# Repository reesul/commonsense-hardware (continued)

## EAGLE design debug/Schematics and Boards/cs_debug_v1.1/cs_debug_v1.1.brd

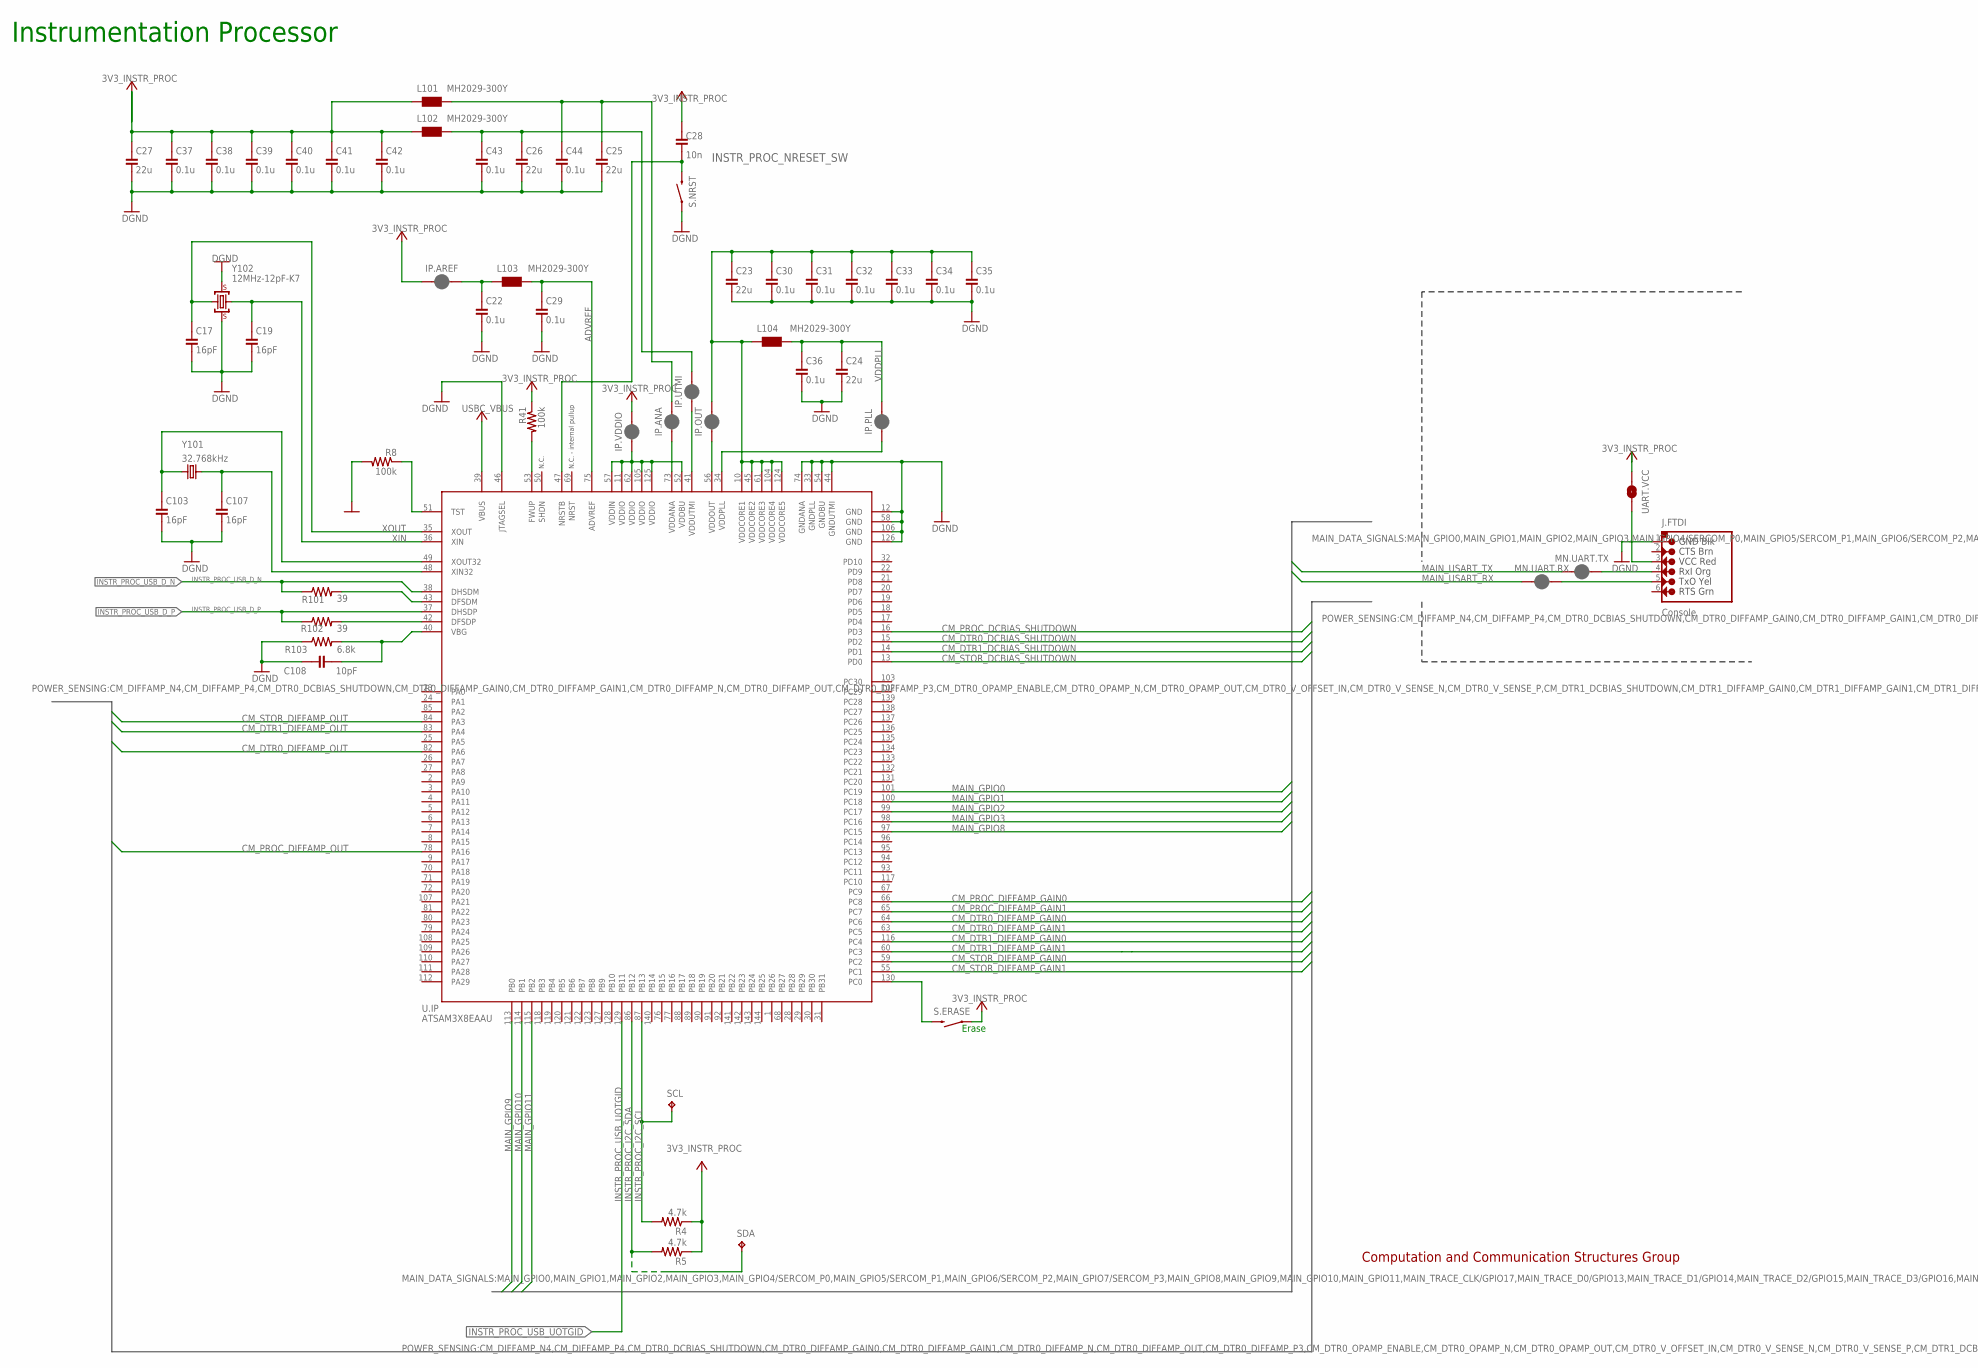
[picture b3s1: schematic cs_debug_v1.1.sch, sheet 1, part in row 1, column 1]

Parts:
C17, C19, C103, C107: 16pF; C0603; MPN C0603C160J5GACTU
C22, C29, C30, C31, C32, C33, C34, C35, C36, C37, C38, C39, C40, C41, C42, C43, C44: 0.1u; C0402; VOLTAGE 10V; MPN C0402C104K8RACTU
C23, C24, C25, C26, C27: 22u; C0805; VOLTAGE 10V; MPN C0805C226M8PAC7800
C28: 10n; C0402; MPN C0402C103K8RACTU
C108: 10pF; C0603; MPN C0603C100K8RAC7867
IP.ANA, IP.AREF, IP.OUT, IP.PLL, IP.UTMI, IP.VDDIO: JUMPER-SMT_2_NC_PASTE_NO-SILK; SMT-JUMPER_2_NC_PASTE_NO-SILK
J.FTDI: J-SERIAL-PORT; HEADER-1X6; PART_NO PH1-06-UA
L101, L102, L103, L104: MH2029-300Y; L0805; PART_NO MH2029-300Y
MN.UART.RX, MN.UART.TX: JUMPER-SMT_2_NC_PASTE_NO-SILK; SMT-JUMPER_2_NC_PASTE_NO-SILK
R4, R5: 4.7k; R0402; MPN ERJ-2GEJ472X
R8, R41: 100k; R0402; MPN RC0402JR-07100KL
R101, R102: 39; R0402; MPN ERJ-2GEJ390X
R103: 6.8k; R0402; MPN ERJ-2GEJ682X
S.ERASE, S.NRST: Momentary; TACTILE_SWITCH_SMD_5.2MM; MPN RS-187R05A2-DS MT RT
SCL: TPTP10SQ; TP10SQ
SDA: TPTP10SQ; TP10SQ
U.IP: ATSAM3X8EA-AU; LQFP144; MPN ATSAM3X8EAAU
UART.VCC: JUMPER-SMT_2_NO_PASTEFREE; SMT-JUMPER_2_NO_PASTEFREE_NO-SILK
Y101: 32.768kHz; CRYSTAL-SMD-3.2X1.5MM; MPN ECS-.327-12.5-34B-TR
Y102: 12MHz-12pF-K7; CRYSTAL-3.2-2.5; MPN ABM8G-12.000MHZ-4Y-T3

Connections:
3V3_INSTR_PROC: C27.1, C28.1, C37.1, C38.1, C39.1, C40.1, C41.1, C42.1, IP.AREF.1, IP.VDDIO.2, L101.1, L102.1, R4.1, R5.1, R41.1, S.ERASE.1, UART.VCC.1; also elsewhere on the board
ADVREF: C29.1, L103.2, U.IP.75 (ADVREF)
ADVREF_PRE: C22.1, IP.AREF.2, L103.1
CM_DTR0_DCBIAS_SHUTDOWN: U.IP.15 (PD2); also elsewhere on the board
CM_DTR0_DIFFAMP_GAIN0: U.IP.64 (PC6); also elsewhere on the board
CM_DTR0_DIFFAMP_GAIN1: U.IP.63 (PC5); also elsewhere on the board
CM_DTR0_DIFFAMP_OUT: U.IP.82 (PA6); also elsewhere on the board
CM_DTR1_DCBIAS_SHUTDOWN: U.IP.14 (PD1); also elsewhere on the board
CM_DTR1_DIFFAMP_GAIN0: U.IP.116 (PC4); also elsewhere on the board
CM_DTR1_DIFFAMP_GAIN1: U.IP.60 (PC3); also elsewhere on the board
CM_DTR1_DIFFAMP_OUT: U.IP.83 (PA4); also elsewhere on the board
CM_PROC_DCBIAS_SHUTDOWN: U.IP.16 (PD3); also elsewhere on the board
CM_PROC_DIFFAMP_GAIN0: U.IP.66 (PC8); also elsewhere on the board
CM_PROC_DIFFAMP_GAIN1: U.IP.65 (PC7); also elsewhere on the board
CM_PROC_DIFFAMP_OUT: U.IP.78 (PA16); also elsewhere on the board
CM_STOR_DCBIAS_SHUTDOWN: U.IP.13 (PD0); also elsewhere on the board
CM_STOR_DIFFAMP_GAIN0: U.IP.59 (PC2); also elsewhere on the board
CM_STOR_DIFFAMP_GAIN1: U.IP.55 (PC1); also elsewhere on the board
CM_STOR_DIFFAMP_OUT: U.IP.84 (PA3); also elsewhere on the board
DGND: C17.2, C19.2, C22.2, C23.2, C24.2, C25.2, C26.2, C27.2, C29.2, C30.2, C31.2, C32.2, C33.2, C34.2, C35.2, C36.2, C37.2, C38.2, C39.2, C40.2, C41.2, C42.2, C43.2, C44.2, C103.2, C107.2, C108.2, J.FTDI.1 (GND), R8.2, R103.1, S.NRST.1, U.IP.12 (GND), U.IP.33 (GNDPLL), U.IP.44 (GNDUTMI), U.IP.46 (JTAGSEL), U.IP.54 (GNDBU), U.IP.58 (GND), U.IP.74 (GNDANA), U.IP.106 (GND), U.IP.126 (GND), Y102.2 (GND), Y102.4 (GND); also elsewhere on the board
ERASE_S: S.ERASE.3 (2), U.IP.130 (PC0)
FWUP: R41.2, U.IP.53 (FWUP)
INSTR_PROC_I2C_SCL: R4.2, SCL.TP, U.IP.87 (PB13); also elsewhere on the board
INSTR_PROC_I2C_SDA: R5.2, SDA.TP, U.IP.86 (PB12); also elsewhere on the board
INSTR_PROC_NRESET_SW: C28.2, S.NRST.3 (2), U.IP.47 (NRSTB)
INSTR_PROC_USB_D_N: R101.1, U.IP.38 (DHSDM); also elsewhere on the board
INSTR_PROC_USB_D_P: R102.1, U.IP.37 (DHSDP); also elsewhere on the board
INSTR_PROC_USB_UOTGID: U.IP.129 (PB11)
MAIN_GPIO0: U.IP.101 (PC19); also elsewhere on the board
MAIN_GPIO1: U.IP.100 (PC18); also elsewhere on the board
MAIN_GPIO2: U.IP.99 (PC17); also elsewhere on the board
MAIN_GPIO3: U.IP.98 (PC16); also elsewhere on the board
MAIN_GPIO8: U.IP.97 (PC15); also elsewhere on the board
MAIN_GPIO9: U.IP.113 (PB0); also elsewhere on the board
MAIN_GPIO10: U.IP.114 (PB1); also elsewhere on the board
MAIN_GPIO11: U.IP.115 (PB2); also elsewhere on the board
MAIN_USART_RX: MN.UART.RX.1; also elsewhere on the board
MAIN_USART_TX: MN.UART.TX.1; also elsewhere on the board
unnamed: R102.2, U.IP.42 (DFSDP)
unnamed: J.FTDI.4 (RX-I), MN.UART.TX.2
unnamed: J.FTDI.5 (TX-O), MN.UART.RX.2
unnamed: J.FTDI.3 (VCC-I), UART.VCC.2
unnamed: R101.2, U.IP.43 (DFSDM)
TST: R8.1, U.IP.51 (TST)
USBC_VBUS: U.IP.39 (VBUS); also elsewhere on the board
VBG: C108.1, R103.2, U.IP.40 (VBG)
VDDANA1: C25.1, C44.1, IP.ANA.2, L101.2
VDDANA_0: IP.ANA.1, U.IP.73 (VDDANA)
VDDIO1: IP.VDDIO.1, U.IP.11 (VDDIO), U.IP.52 (VDDBU), U.IP.57 (VDDIN), U.IP.62 (VDDIO), U.IP.105 (VDDIO), U.IP.125 (VDDIO)
VDDOUT: C23.1, C30.1, C31.1, C32.1, C33.1, C34.1, C35.1, IP.OUT.2, L104.1, U.IP.10 (VDDCORE1), U.IP.45 (VDDCORE2), U.IP.61 (VDDCORE3), U.IP.104 (VDDCORE4), U.IP.124 (VDDCORE5)
VDDOUTMI: C26.1, C43.1, IP.UTMI.2, L102.2
VDDOUTMI_0: IP.UTMI.1, U.IP.41 (VDDUTMI)
VDDOUT_0: IP.OUT.1, U.IP.56 (VDDOUT)
VDDPLL: C24.1, C36.1, IP.PLL.2, L104.2
VDDPLL_0: IP.PLL.1, U.IP.34 (VDDPLL)
XIN: C19.1, U.IP.36 (XIN), Y102.1 (C1)
XIN32: C107.1, U.IP.48 (XIN32), Y101.P$1 (1)
XOUT: C17.1, U.IP.35 (XOUT), Y102.3 (C2)
XOUT32: C103.1, U.IP.49 (XOUT32), Y101.P$2 (2)

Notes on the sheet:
N.C.
N.C. - internal pullup
Instrumentation Processor
Computation and Communication Structures Group
Erase

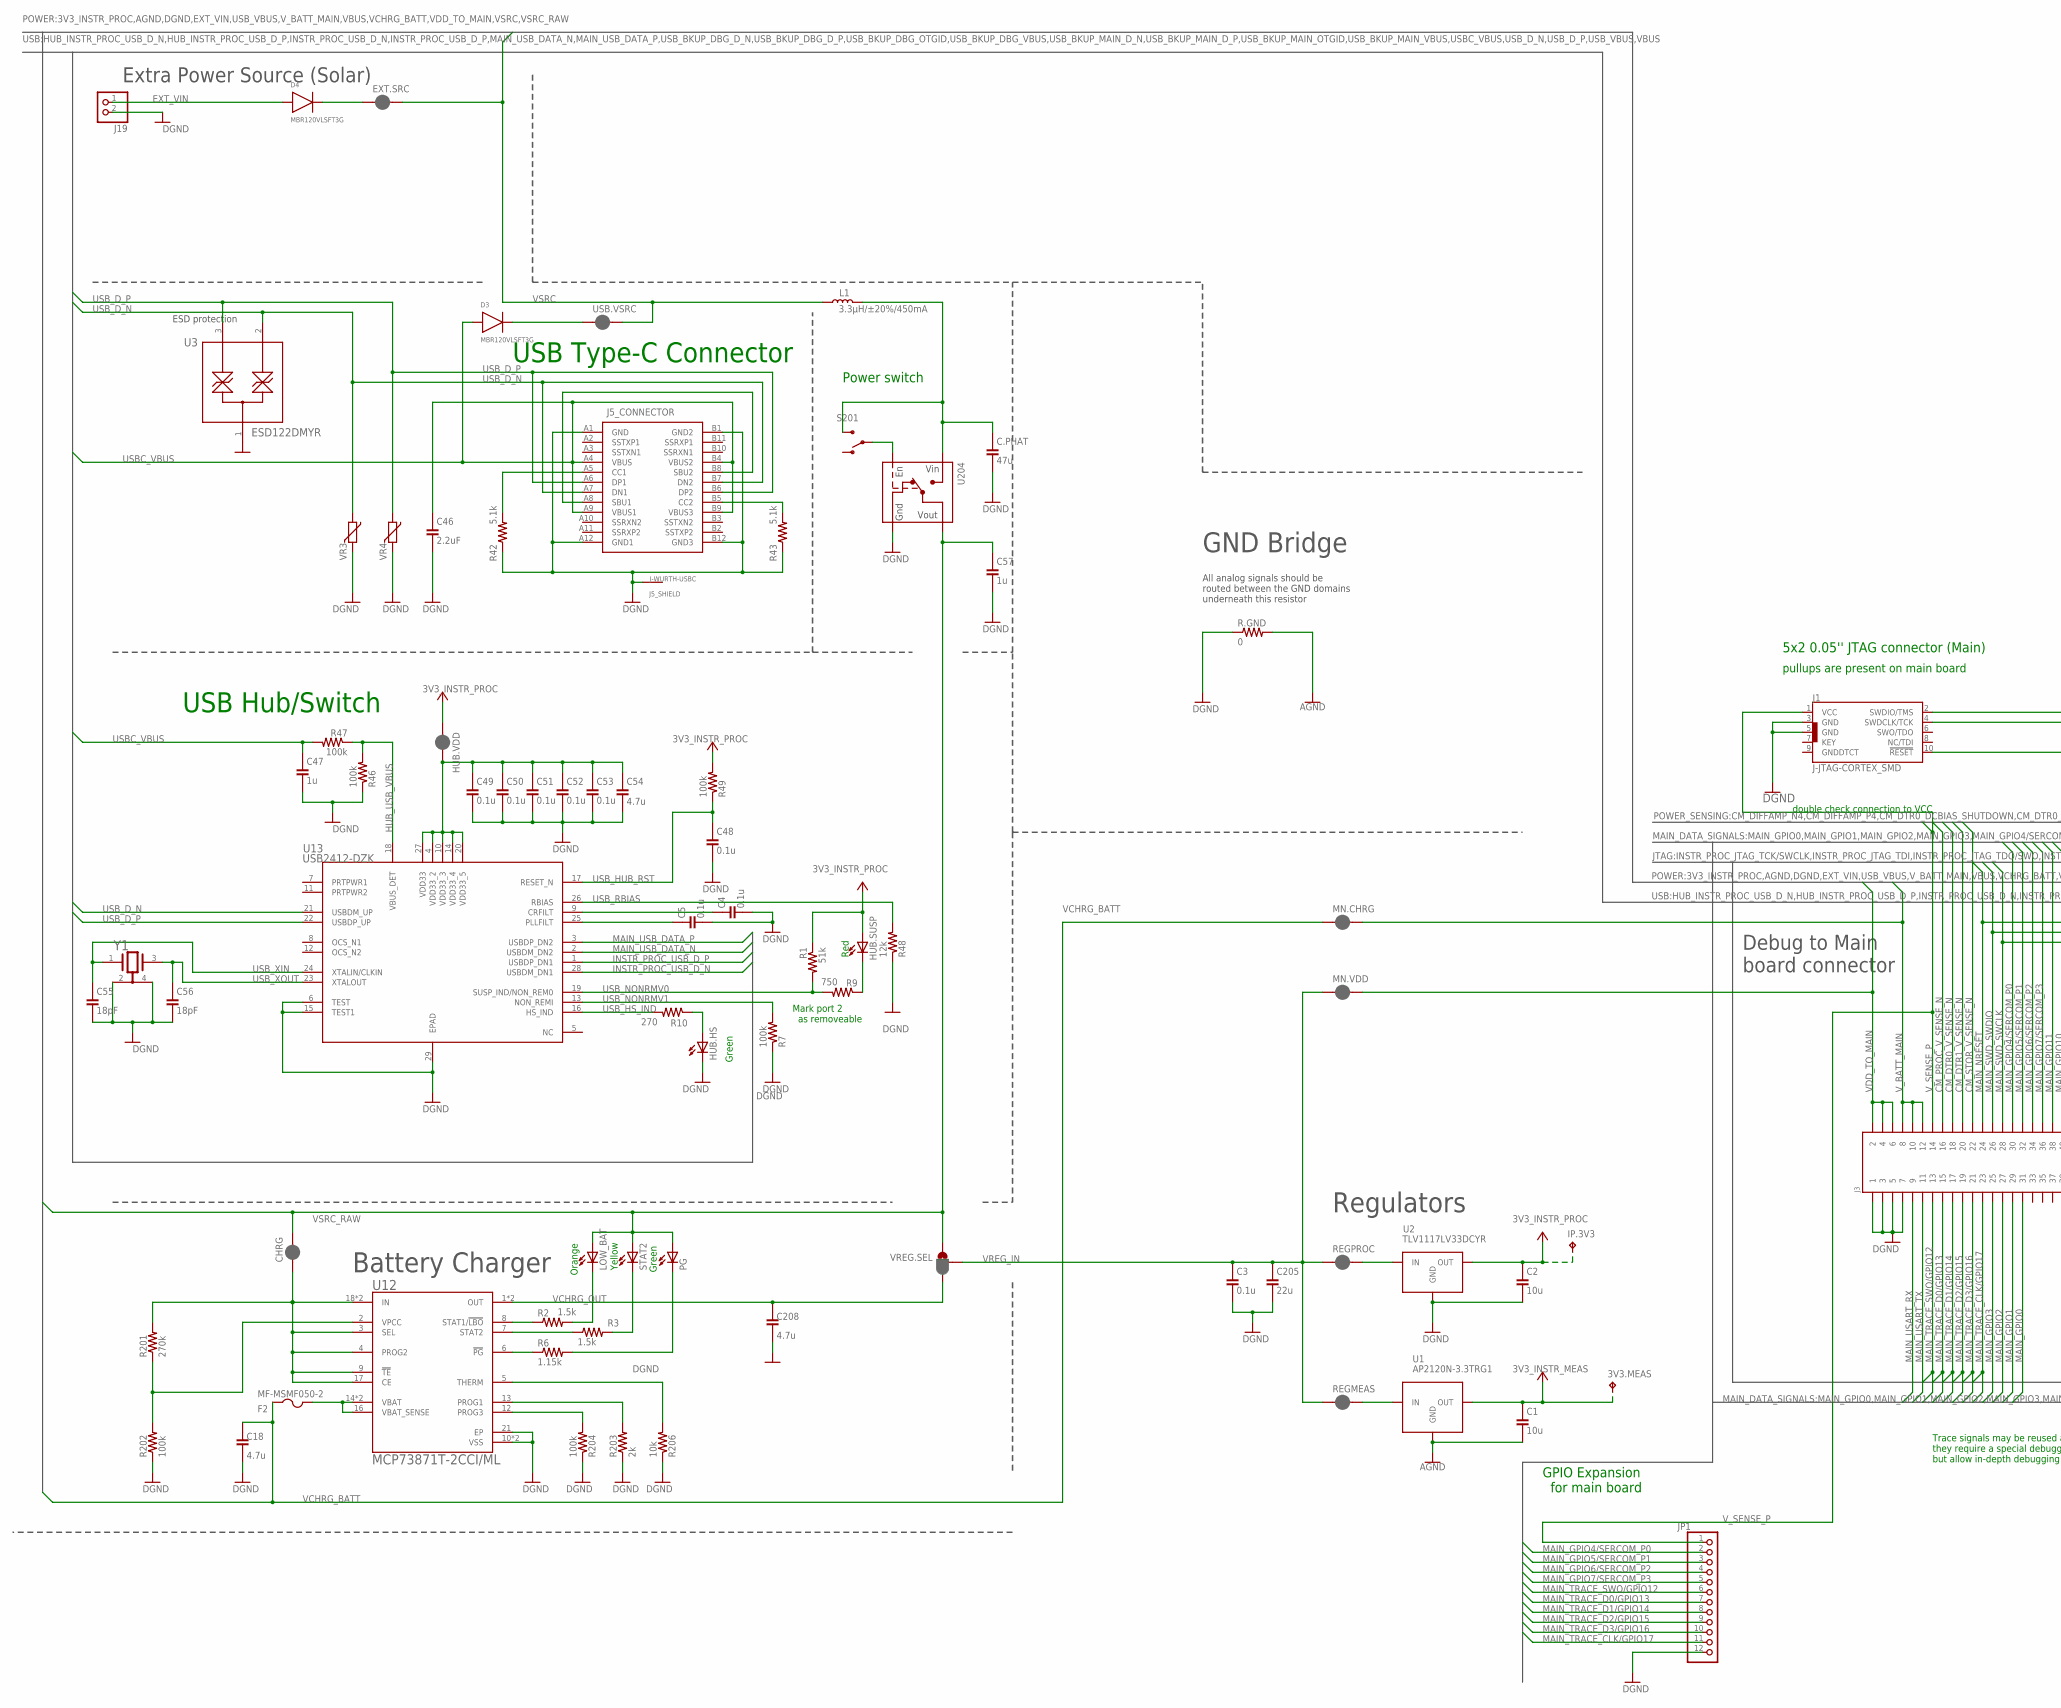
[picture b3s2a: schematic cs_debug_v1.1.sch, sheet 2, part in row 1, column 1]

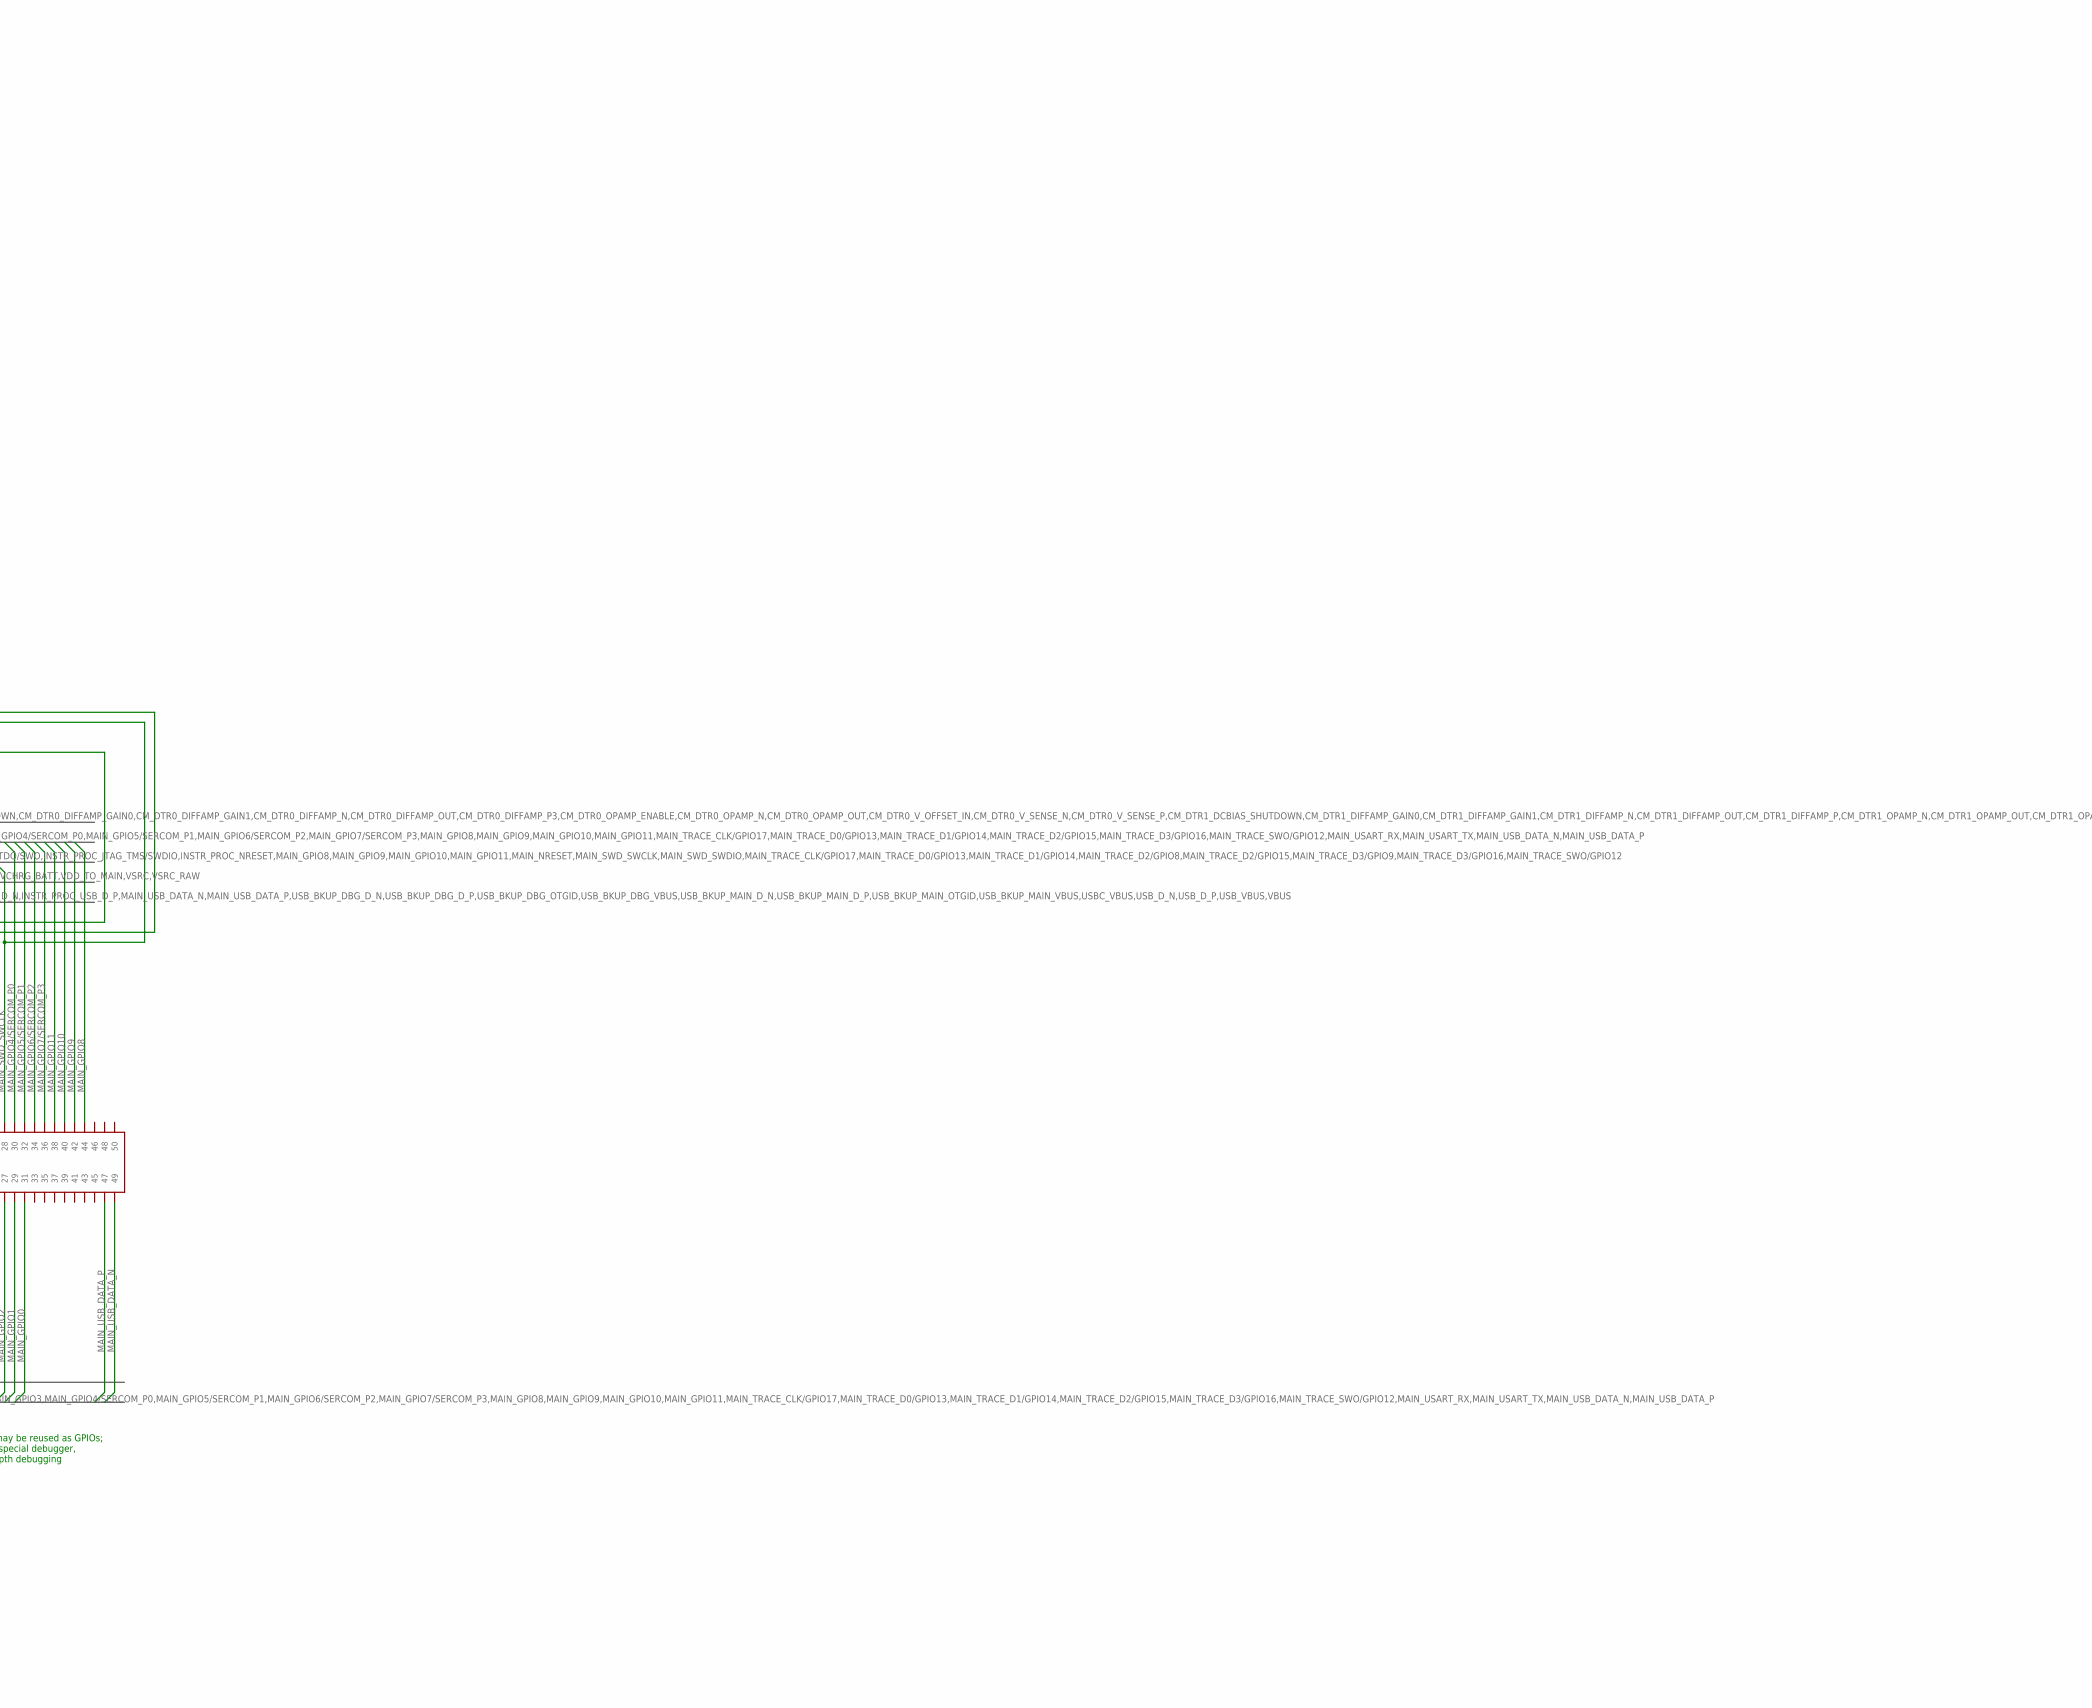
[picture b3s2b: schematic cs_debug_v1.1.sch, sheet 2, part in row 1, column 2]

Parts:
3V3.MEAS: TPTP10SQ; TP10SQ
C1, C2: 10u; C0805; VOLTAGE 10V; MPN C0805C106M8RACTU
C3, C4, C5, C48, C49, C50, C51, C52, C53: 0.1u; C0402; VOLTAGE 10V; MPN C0402C104K8RACTU
C18, C54, C208: 4.7u; C0603; MPN C0603C475M8PACTU
C46: 2.2uF; C0603; MPN C0603C225K8RACTU
C47: 1u; C0402; VOLTAGE 10V; MPN C0402C105K8PACTU
C55, C56: 18pF; C0402; MPN C0402C180J8GAC7867
C57: 1u; C0402; VOLTAGE 10V; PART_NO C0402C105M8PACTU
C205: 22u; C0805; VOLTAGE 10V; MPN C0805C226M8PAC7800
C.PHAT: 47u; C1206; VOLTAGE 10V; MPN C1206C476M8PACTU
CHRG: JUMPER-SMT_2_NC_PASTE_NO-SILK; SMT-JUMPER_2_NC_PASTE_NO-SILK
D3, D4: MBR120VLSFT3G; SOD-123
EXT.SRC: JUMPER-SMT_2_NC_PASTE_NO-SILK; SMT-JUMPER_2_NC_PASTE_NO-SILK
F2: MF-MSMF050-2; 1812; MPN MF-MSMF050-2
HUB.HS: LEDCHIPLED_0603; CHIPLED_0603; MPN LT Q39G-Q1OO-25-1
HUB.SUSP: LEDCHIPLED_0603; CHIPLED_0603; MPN 150060RS75000
HUB.VDD: JUMPER-SMT_2_NC_PASTE_NO-SILK; SMT-JUMPER_2_NC_PASTE_NO-SILK
IP.3V3: TPTP10SQ; TP10SQ
J1: J-JTAG-CORTEX_SMD; SAMTECH_FTSH-105-01; PART_NO FTSH-105-01-L-DV-K-TR
J3: HIROSE-DF40_50-PIN_CONNECTORS-HEADER; HRS_DF40C-50DP-0.4V(51); MPN DF40C-50DP-0.4V(51)
J5: J-WURTH-USBC; 632723X00011; MPN 632723300011
J19: Solar; JST-PH-2-SMT-RA; PART_NO S2B-PH-SM4-TB(LF)(SN)
JP1: J-HEADER-1X12; 1X12_ROUND; MPN TSW-112-07-T-S
L1: 3.3µH/±20%/450mA; 0805; MPN MLZ2012A3R3WT000
LOW_BAT: LEDCHIPLED_0603; CHIPLED_0603; MPN LO Q976-PS-25-0-20-R18
MN.CHRG, MN.VDD: JUMPER-SMT_2_NC_PASTE_NO-SILK; SMT-JUMPER_2_NC_PASTE_NO-SILK
PG: LEDCHIPLED_0603; CHIPLED_0603; MPN LT Q39G-Q1OO-25-1
R1: 51k; R0402; MPN ERJ-2GEJ513X
R2, R3: 1.5k; R0402; MPN ERJ-2GEJ152X
R6: 1.15k; R0402; MPN ERJ-2RKF1151X
R7, R46, R47, R49, R202, R204: 100k; R0402; MPN ERJ-2GEJ104X
R9: 750; R0402; MPN ERJ-U02J751X
R10: 270; R0402; MPN ERJ-2GEJ271X
R42, R43: 5.1k; R0603; MPN ERJ-3EKF5101V
R48: 12k; R0402; MPN ERJ-2RKF1202X
R201: 270k; R0402; MPN ERJ-2GEJ274X
R203: 2k; R0402; MPN ERJ-2GEJ202X
R206: 10k; R0402; MPN ERJ-2GEJ103X
R.GND: 0; R2010; MPN ERJ-S1D0R00U
REGMEAS: JUMPER-SMT_2_NC_PASTE_NO-SILK; SMT-JUMPER_2_NC_PASTE_NO-SILK
REGPROC: JUMPER-SMT_2_NC_PASTE_NO-SILK; SMT-JUMPER_2_NC_PASTE_NO-SILK
S201: SLIDESWITCH-SPDT-SMD-RIGHT-ANGLE; SWITCH_SPST_SMD_A; PART_NO CUS-12TB
STAT2: LEDCHIPLED_0603; CHIPLED_0603; MPN LY Q396-P1Q2-36
U1: AP2120N-3.3TRG1; SOT23-3_AP2120N; MPN AP2120N-3.3TRG1
U2: TLV1117LV33DCYR; DCY4
U3: ESD122DMYR; DMY0003A
U12: MCP73871T-2CCI/ML; QFN50P400X400X100-21N; MPN MCP73871T-2CCI/ML
U13: USB2412-DZK; QFN28_5X5MC_MCH
U204: LOADSWITCH-MIC94164; WLCSP6_2X3; PART_NO MIC94164YCS-TR
USB.VSRC: JUMPER-SMT_2_NC_PASTE_NO-SILK; SMT-JUMPER_2_NC_PASTE_NO-SILK
VR3, VR4: VARISTOR; R0603; PART_NO CG0603MLC-05E
VREG.SEL: JUMPER-SMT_3_1-NC_PASTE_NO-SILK; SMT-JUMPER_3_1-NC_PASTE_NO-SILK
Y1: EPSON_TSX-3225_24.0000MF10Z-C3; XTAL_EPSON_TSX3225; MPN TSX-3225 24.0000MF10Z-C3

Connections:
3V3_INSTR_MEAS: 3V3.MEAS.TP, C1.1, U1.OUT; also elsewhere on the board
3V3_INSTR_PROC: C2.1, HUB.SUSP.A, HUB.VDD.1, IP.3V3.TP, R1.1, R49.2, U2.OUT, U2.OUT_TAB (OUT); also elsewhere on the board
AGND: C1.2, R.GND.2, U1.GND; also elsewhere on the board
BAT_CHG_PROG1: R203.2, U12.13 (PROG1)
CC3: J5.A5 (CC1), R42.2
CC4: J5.B5 (CC2), R43.2
CHG_VPCC: R201.1, R202.2, U12.2 (VPCC)
CM_DTR0_V_SENSE_N: J3.18; also elsewhere on the board
CM_DTR1_V_SENSE_N: J3.20; also elsewhere on the board
CM_PROC_V_SENSE_N: J3.16; also elsewhere on the board
CM_STOR_V_SENSE_N: J3.22; also elsewhere on the board
DGND: C2.2, C3.2, C4.2, C5.2, C18.2, C46.2, C47.2, C48.2, C49.2, C50.2, C51.2, C52.2, C53.2, C54.2, C55.2, C56.2, C57.2, C205.2, C208.2, C.PHAT.2, HUB.HS.C, J1.3 (GND), J1.5 (GND), J3.1, J3.3, J3.5, J3.7, J5.A1 (GND), J5.A12 (GND1), J5.B1 (GND2), J5.B12 (GND3), J5.GND (SHIELD), J5.GND1 (SHIELD), J5.Z1 (SHIELD), J5.Z2 (SHIELD), J5.Z3 (SHIELD), J5.Z4 (SHIELD), J5.Z5 (SHIELD), J5.Z6 (SHIELD), J19.2 (1), JP1.12, R7.1, R42.1, R43.1, R46.1, R48.1, R202.1, R203.1, R204.1, R206.1, R.GND.1, U2.GND, U3.1 (GND), U12.10 (VSS), U12.11 (VSS), U12.21 (EP), U13.6 (TEST), U13.15 (TEST1), U13.29 (EPAD), U204.C1 (GND), VR3.2, VR4.2, Y1.2 (1_GND), Y1.4 (2_GND); also elsewhere on the board
EXT_VIN: D4.A, J19.1 (2)
HUB_USB_VBUS: R46.2, R47.1, U13.18 (VBUS_DET)
INSTR_PROC_USB_D_N: U13.28 (USBDM_DN1); also elsewhere on the board
INSTR_PROC_USB_D_P: U13.1 (USBDP_DN1); also elsewhere on the board
MAIN_GPIO0: J3.31; also elsewhere on the board
MAIN_GPIO1: J3.29; also elsewhere on the board
MAIN_GPIO2: J3.27; also elsewhere on the board
MAIN_GPIO3: J3.25; also elsewhere on the board
MAIN_GPIO4/SERCOM_P0: J3.30, JP1.2
MAIN_GPIO5/SERCOM_P1: J3.32, JP1.3
MAIN_GPIO6/SERCOM_P2: J3.34, JP1.4
MAIN_GPIO7/SERCOM_P3: J3.36, JP1.5
MAIN_GPIO8: J3.44; also elsewhere on the board
MAIN_GPIO9: J3.42; also elsewhere on the board
MAIN_GPIO10: J3.40; also elsewhere on the board
MAIN_GPIO11: J3.38; also elsewhere on the board
MAIN_NRESET: J1.10 (!RESET), J3.24
MAIN_SWD_SWCLK: J1.4 (SWDCLK/TCK), J3.28
MAIN_SWD_SWDIO: J1.2 (SWDIO/TMS), J3.26
MAIN_TRACE_CLK/GPIO17: J3.23, JP1.11
MAIN_TRACE_D0/GPIO13: J3.15, JP1.7
MAIN_TRACE_D1/GPIO14: J3.17, JP1.8
MAIN_TRACE_D2/GPIO15: J3.19, JP1.9
MAIN_TRACE_D3/GPIO16: J3.21, JP1.10
MAIN_TRACE_SWO/GPIO12: J3.13, JP1.6
MAIN_USART_RX: J3.9; also elsewhere on the board
MAIN_USART_TX: J3.11; also elsewhere on the board
MAIN_USB_DATA_N: J3.49, U13.2 (USBDM_DN2)
MAIN_USB_DATA_P: J3.47, U13.3 (USBDP_DN2)
unnamed: REGMEAS.2, U1.IN
unnamed: HUB.SUSP.C, R9.1
unnamed: REGPROC.2, U2.IN
unnamed: LOW_BAT.C, R2.2
unnamed: F2.2, U12.14 (VBAT), U12.15 (VBAT), U12.16 (VBAT_SENSE)
unnamed: R204.2, U12.12 (PROG3)
unnamed: R2.1, U12.8 (STAT1/!LBO)
unnamed: R3.1, U12.7 (STAT2)
unnamed: D4.C (N), EXT.SRC.1
unnamed: C4.1, U13.9 (CRFILT)
unnamed: C5.1, U13.25 (PLLFILT)
unnamed: R3.2, STAT2.C
unnamed: PG.C, R6.2
unnamed: R6.1, U12.6 (!PG)
unnamed: HUB.HS.A, R10.1
unnamed: CHRG.1, R201.2, U12.3 (SEL), U12.4 (PROG2), U12.9 (!TE), U12.17 (CE), U12.18 (IN), U12.19 (IN)
THERM: R206.2, U12.5 (THERM)
UCTX_DBGRX: J5.A8 (SBU1), J5.B8 (SBU2)
USBC_VBUS: C46.1, C47.1, D3.A, J5.A4 (VBUS), J5.A9 (VBUS1), J5.B4 (VBUS2), J5.B9 (VBUS3), R47.2; also elsewhere on the board
USB_D_N: J5.A7 (DN1), J5.B7 (DN2), U3.2 (IO2), U13.21 (USBDM_UP), VR3.1
USB_D_P: J5.A6 (DP1), J5.B6 (DP2), U3.3 (IO1), U13.22 (USBDP_UP), VR4.1
USB_HS_IND: R10.2, U13.16 (HS_IND)
USB_HUB_RST: C48.1, R49.1, U13.17 (RESET_N)
USB_HUB_VDD: C49.1, C50.1, C51.1, C52.1, C53.1, C54.1, HUB.VDD.2, U13.4 (VDD33_2), U13.10 (VDD33_3), U13.14 (VDD33_4), U13.20 (VDD33_5), U13.27 (VDD33)
USB_NONRMV0: R1.2, R9.2, U13.19 (SUSP_IND/NON_REM0)
USB_NONRMV1: R7.2, U13.13 (NON_REMI)
USB_RBIAS: R48.2, U13.26 (RBIAS)
USB_XIN: C55.1, U13.24 (XTALIN/CLKIN), Y1.1
USB_XOUT: C56.1, U13.23 (XTALOUT), Y1.3
VCHRG_BATT: C18.1, F2.1, MN.CHRG.1
VCHRG_OUT: C208.1, U12.1 (OUT), U12.20 (OUT), VREG.SEL.3
VDD_TO_MAIN: J3.2, J3.4, J3.6, MN.VDD.2
VREG.SW.EN: S201.2, U204.C2 (ENABLE)
VREG_IN: C3.1, C205.1, MN.VDD.1, REGMEAS.1, REGPROC.1, VREG.SEL.2
VSRC: EXT.SRC.2, L1.1, USB.VSRC.2
VSRC_RAW: C57.1, CHRG.2, LOW_BAT.A, PG.A, STAT2.A, U204.A1 (VOUT), U204.B1 (VOUT), VREG.SEL.1
VSRC_SW: C.PHAT.1, L1.2, S201.3 (S), U204.A2 (VIN), U204.B2 (VIN)
VUSB_DIODE: D3.C (N), USB.VSRC.1
V_BATT_MAIN: J3.8, J3.10, J3.12, MN.CHRG.2
V_SENSE_P: J1.1 (VCC), J3.14, JP1.1; also elsewhere on the board

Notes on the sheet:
Debug to Main board connector
Trace signals may be reused as GPIOs; they require a special debugger, but allow in-depth debugging
All analog signals should be routed between the GND domains underneath this resistor
5x2 0.05'' JTAG connector (Main)
pullups are present on main board
Battery Charger
Power switch
Extra Power Source (Solar)
Regulators
GND Bridge
USB Type-C Connector
ESD protection
USB Hub/Switch
Orange
Yellow
Green
Red
GPIO Expansion for main board
Mark port 2 as removeable
double check connection to VCC
